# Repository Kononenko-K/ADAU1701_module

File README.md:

# ADAU1701_module
SigmaDSP audio module with SigmaLink-USBi compatible programmer and USB digital isolator included
<br/>

## Overview
This is a part of my yet unfinished project, that's why the board has such a peculiar shape. But it can be used as a standalone audio processing device with external PC control.
## [Hardware](Hardware)
The board features AUAD1701 SigmaDSP chip, CY7C68013A based USBi programmer and ADUM4160 USB isolator that prevents ground loops when the PC USB port and audio source share the same ground. It also has an active second order low pass reconstruction filter on the DAC outputs. The board can be programmed with SigmaStudio. There are [KiCad project](/Hardware), [Gerber files](/Hardware/gbr) and [PDF](/Hardware/project.pdf) avaliable.

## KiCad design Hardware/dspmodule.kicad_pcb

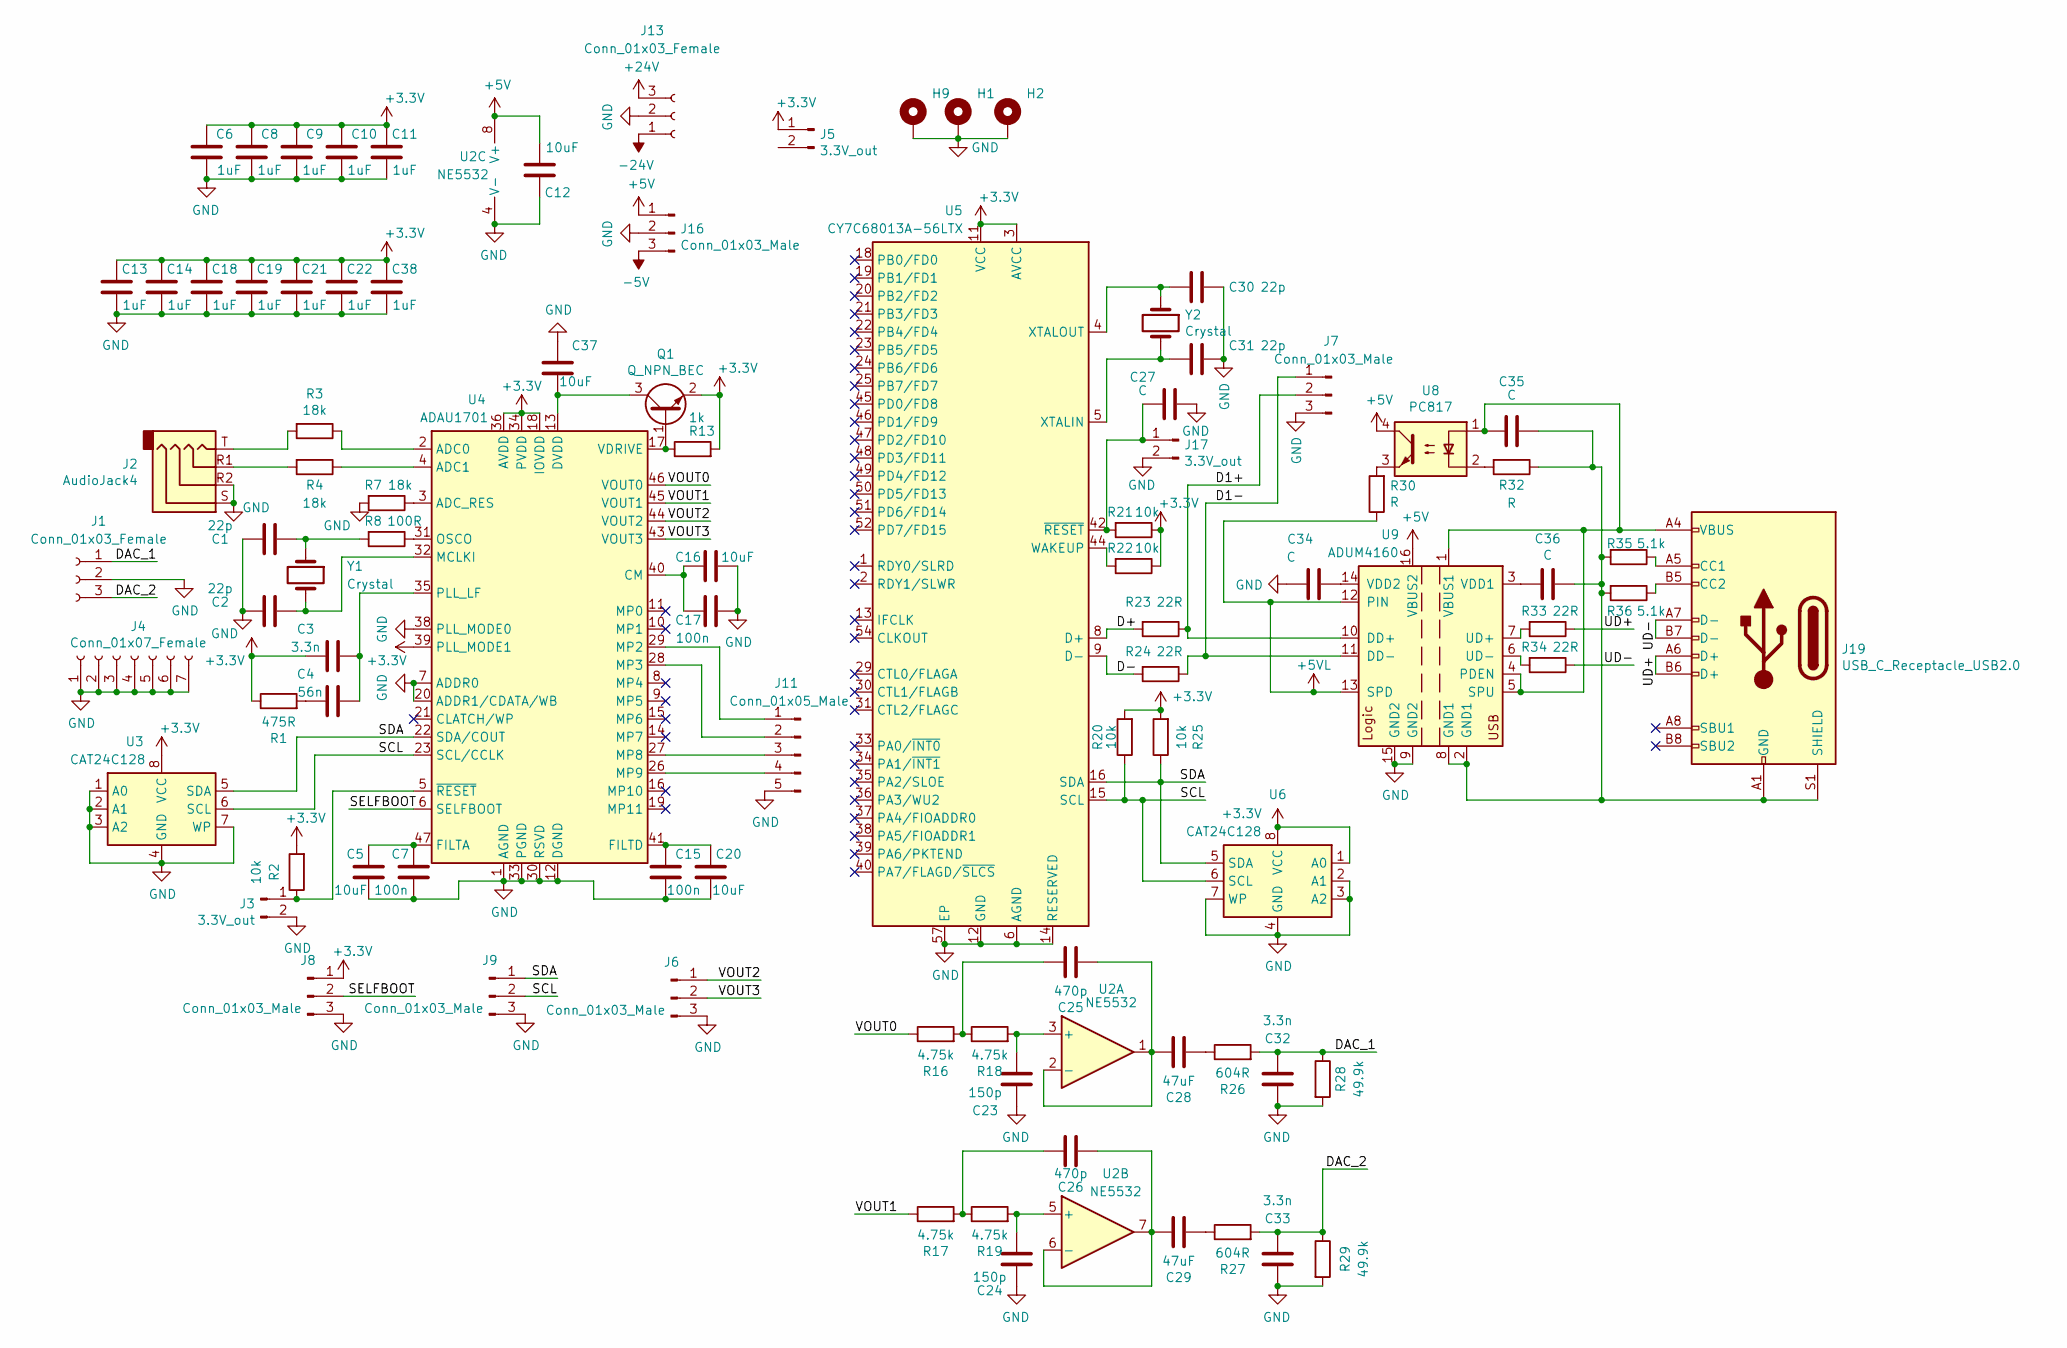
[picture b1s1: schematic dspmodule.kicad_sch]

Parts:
C1, C2, C30, C31: 22p; C_1206_3216Metric_Pad1.33x1.80mm_HandSolder
C3, C32, C33: 3.3n; C_1206_3216Metric_Pad1.33x1.80mm_HandSolder
C4: 56n; C_1206_3216Metric_Pad1.33x1.80mm_HandSolder
C5, C12, C16, C20: 10uF; C_1206_3216Metric_Pad1.33x1.80mm_HandSolder
C6, C8, C9, C10, C11, C13, C14, C18, C19, C21, C22, C38: 1uF; C_0603_1608Metric_Pad1.08x0.95mm_HandSolder
C7, C15, C17: 100n; C_1206_3216Metric_Pad1.33x1.80mm_HandSolder
C23, C24: 150p; C_1206_3216Metric_Pad1.33x1.80mm_HandSolder
C25, C26: 470p; C_1206_3216Metric_Pad1.33x1.80mm_HandSolder
C27, C34, C35, C36: C; C_1206_3216Metric_Pad1.33x1.80mm_HandSolder
C28, C29: 47uF; C_1206_3216Metric_Pad1.33x1.80mm_HandSolder
C37: 10uF; C_0603_1608Metric_Pad1.08x0.95mm_HandSolder
H1, H2, H9: MountingHole_Pad; MountingHole_3.2mm_M3_DIN965_Pad
J1, J13: Conn_01x03_Female; PinSocket_1x03_P2.54mm_Vertical
J2: AudioJack4; Jack_3.5mm_PJ320D_Horizontal
J3, J5, J17: 3.3V_out; PinHeader_1x02_P2.54mm_Vertical
J4: Conn_01x07_Female; PinSocket_1x07_P2.54mm_Vertical
J6, J7, J8, J9, J16: Conn_01x03_Male; PinHeader_1x03_P2.54mm_Vertical
J11: Conn_01x05_Male; PinSocket_1x05_P2.54mm_Vertical
J19: USB_C_Receptacle_USB2.0; USB_C_Receptacle_Palconn_UTC16-G
Q1: Q_NPN_BEC; SOT-23
R1: 475R; R_1206_3216Metric_Pad1.30x1.75mm_HandSolder
R2, R20, R21, R22, R25: 10k; R_1206_3216Metric_Pad1.30x1.75mm_HandSolder
R3, R4, R7: 18k; R_1206_3216Metric_Pad1.30x1.75mm_HandSolder
R8: 100R; R_1206_3216Metric_Pad1.30x1.75mm_HandSolder
R13: 1k; R_1206_3216Metric_Pad1.30x1.75mm_HandSolder
R16, R17, R18, R19: 4.75k; R_1206_3216Metric_Pad1.30x1.75mm_HandSolder
R23, R24, R33, R34: 22R; R_1206_3216Metric_Pad1.30x1.75mm_HandSolder
R26, R27: 604R; R_1206_3216Metric_Pad1.30x1.75mm_HandSolder
R28, R29: 49.9k; R_1206_3216Metric_Pad1.30x1.75mm_HandSolder
R30, R32: R; R_1206_3216Metric_Pad1.30x1.75mm_HandSolder
R35, R36: 5.1k; R_1206_3216Metric_Pad1.30x1.75mm_HandSolder
U2: NE5532; SOIC-8_3.9x4.9mm_P1.27mm
U3, U6: CAT24C128; SOIC-8_3.9x4.9mm_P1.27mm
U4: ADAU1701; LQFP-48_7x7mm_P0.5mm
U5: CY7C68013A-56LTX; QFN-56-1EP_8x8mm_P0.5mm_EP4.5x5.2mm_ThermalVias_TopTented
U8: PC817; DIP-4_W7.62mm
U9: ADUM4160; SOIC-16W_7.5x10.3mm_P1.27mm
Y1, Y2: Crystal; Crystal_SMD_HC49-SD

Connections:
+3V3: C3.2, C6.1, C8.1, C9.1, C10.1, C11.1, C13.1, C14.1, C18.1, C19.1, C21.1, C22.1, C38.1, J5.1, J8.1, Q1.2 (E), R1.1, R2.2, R13.2, R20.2, R21.1, R22.1, R25.2, U3.8 (VCC), U4.18 (IOVDD), U4.34 (PVDD), U4.36 (AVDD), U4.39 (PLL_MODE1), U4.48 (AVDD), U5.3 (AVCC), U5.7 (AVCC), U5.11 (VCC), U5.17 (VCC), U5.27 (VCC), U5.32 (VCC), U5.43 (VCC), U5.55 (VCC), U6.1 (A0), U6.8 (VCC)
+5V: C12.1, J16.1, U2.8 (V+), U8.4, U9.16 (VBUS2)
+5VL: R30.1, U9.12 (PIN), U9.13 (SPD)
+24V: J13.3
-5V: J16.3
-24V: J13.1
/D1+: J7.2, R23.1, U9.10 (DD+)
/D1-: J7.1, R24.1, U9.11 (DD-)
/D+: R23.2, U5.8 (D+)
/D-: R24.2, U5.9 (D-)
/DAC_1: C32.1, J1.1, R26.2, R28.1
/DAC_2: C33.1, J1.3, R27.2, R29.1
/SCL: J9.2, R20.1, U3.6 (SCL), U4.23 (SCL/CCLK), U5.15 (SCL), U6.6 (SCL)
/SDA: J9.1, R25.1, U3.5 (SDA), U4.22 (SDA/COUT), U5.16 (SDA), U6.5 (SDA)
/SELFBOOT: J8.2, U4.6 (SELFBOOT)
/UD+: J19.A6 (D+), J19.B6 (D+), R33.1
/UD-: J19.A7 (D-), J19.B7 (D-), R34.1
/VOUT0: R16.1, U4.46 (VOUT0)
/VOUT1: R17.1, U4.45 (VOUT1)
/VOUT2: J6.1, U4.44 (VOUT2)
/VOUT3: J6.2, U4.43 (VOUT3)
GND: C1.1, C2.1, C5.1, C6.2, C7.1, C8.2, C9.2, C10.2, C11.2, C12.2, C13.2, C14.2, C15.1, C16.2, C17.2, C18.2, C19.2, C20.1, C21.2, C22.2, C23.1, C24.1, C27.2, C30.2, C31.2, C32.2, C33.2, C34.2, C37.1, C38.2, H1.1, H2.1, H9.1, J1.2, J2.R2, J2.S, J3.2, J4.1, J4.2, J4.3, J4.4, J4.5, J4.6, J4.7, J6.3, J7.3, J8.3, J9.3, J11.5, J13.2, J16.2, J17.2, R7.2, R28.2, R29.2, U2.4 (V-), U3.1 (A0), U3.2 (A1), U3.3 (A2), U3.4 (GND), U3.7 (WP), U4.1 (AGND), U4.7 (ADDR0), U4.12 (DGND), U4.20 (ADDR1/CDATA/WB), U4.25 (DGND), U4.30 (RSVD), U4.33 (PGND), U4.37 (AGND), U4.38 (PLL_MODE0), U4.42 (AGND), U5.6 (AGND), U5.10 (AGND), U5.12 (GND), U5.14 (RESERVED), U5.26 (GND), U5.28 (GND), U5.41 (GND), U5.53 (GND), U5.56 (GND), U5.57 (EP), U6.2 (A1), U6.3 (A2), U6.4 (GND), U6.7 (WP), U9.9 (GND2), U9.15 (GND2)
unnamed: C1.2, R8.2, Y1.1
unnamed: C2.2, U4.32 (MCLKI), Y1.2
unnamed: C3.1, C4.1, U4.35 (PLL_LF)
unnamed: C4.2, R1.2
unnamed: C5.2, C7.2, U4.47 (FILTA)
unnamed: C15.2, C20.2, U4.41 (FILTD)
unnamed: C16.1, C17.1, U4.40 (CM)
unnamed: C23.2, R18.2, U2.3 (+)
unnamed: C24.2, R19.2, U2.5 (+)
unnamed: C25.1, R16.2, R18.1
unnamed: C25.2, C28.1, U2.1, U2.2 (-)
unnamed: C26.1, R17.2, R19.1
unnamed: C26.2, C29.1, U2.6 (-), U2.7
unnamed: C27.1, J17.1, R21.2, U5.42 (~RESET)
unnamed: C28.2, R26.1
unnamed: C29.2, R27.1
unnamed: C30.1, U5.4 (XTALOUT), Y2.1
unnamed: C31.1, U5.5 (XTALIN), Y2.2
unnamed: C34.1, U9.14 (VDD2)
unnamed: C35.1, C36.1, J19.A1 (GND), J19.A12 (GND), J19.B1 (GND), J19.B12 (GND), J19.S1 (SHIELD), R32.1, R35.2, R36.2, U9.2 (GND1), U9.8 (GND1)
unnamed: C35.2, J19.A4 (VBUS), J19.A9 (VBUS), J19.B4 (VBUS), J19.B9 (VBUS), U8.1, U9.1 (VBUS1), U9.4 (PDEN), U9.5 (SPU)
unnamed: C36.2, U9.3 (VDD1)
unnamed: C37.2, Q1.3 (C), U4.13 (DVDD), U4.24 (DVDD)
unnamed: J2.R1, R4.2
unnamed: J2.T, R3.2
unnamed: J3.1, R2.1, U4.5 (~RESET)
unnamed: J11.1, U4.29 (MP2)
unnamed: J11.2, U4.28 (MP3)
unnamed: J11.3, U4.27 (MP8)
unnamed: J11.4, U4.26 (MP9)
unnamed: J19.A5 (CC1), R35.1
unnamed: J19.B5 (CC2), R36.1
unnamed: Q1.1 (B), R13.1, U4.17 (VDRIVE)
unnamed: R3.1, U4.2 (ADC0)
unnamed: R4.1, U4.4 (ADC1)
unnamed: R7.1, U4.3 (ADC_RES)
unnamed: R8.1, U4.31 (OSCO)
unnamed: R22.2, U5.44 (WAKEUP)
unnamed: R30.2, U8.3
unnamed: R32.2, U8.2
unnamed: R33.2, U9.7 (UD+)
unnamed: R34.2, U9.6 (UD-)

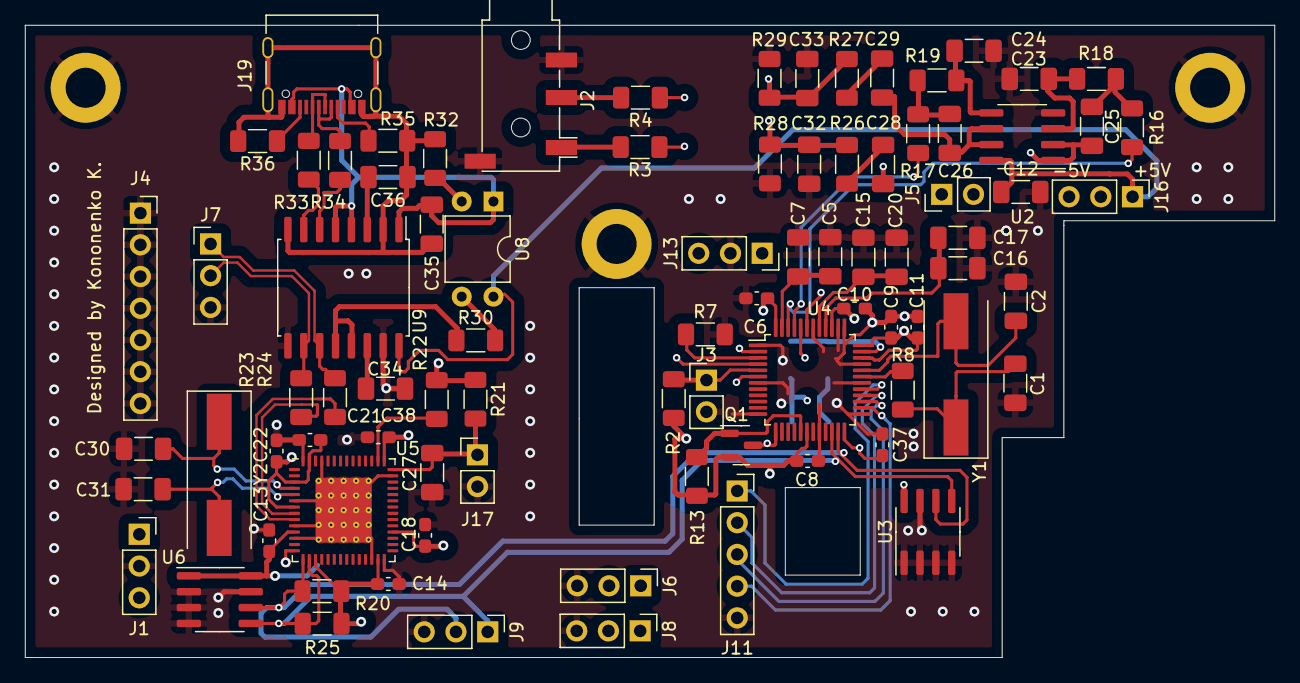
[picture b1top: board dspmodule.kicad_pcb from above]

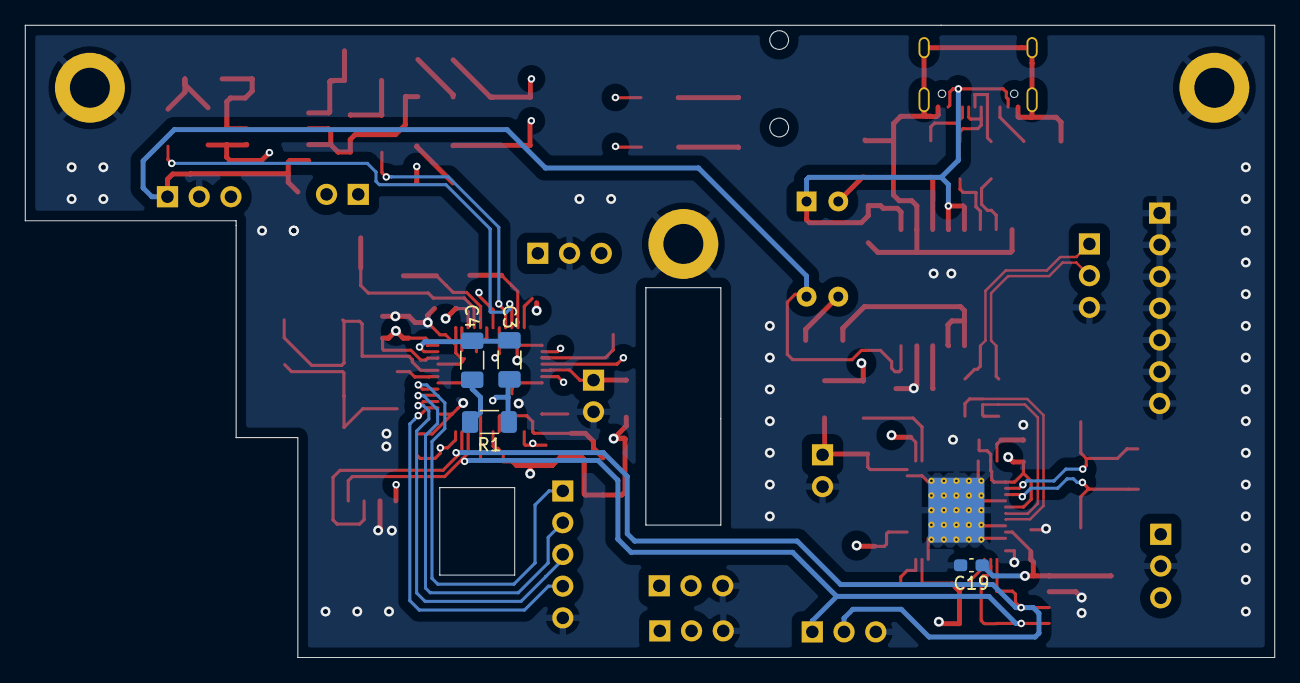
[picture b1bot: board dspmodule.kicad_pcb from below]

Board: 4 copper layers, 100.0 x 50.6 mm, 92 parts (4 on the bottom side), 61 nets.

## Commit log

2023-09-05 Update README.md
    -
